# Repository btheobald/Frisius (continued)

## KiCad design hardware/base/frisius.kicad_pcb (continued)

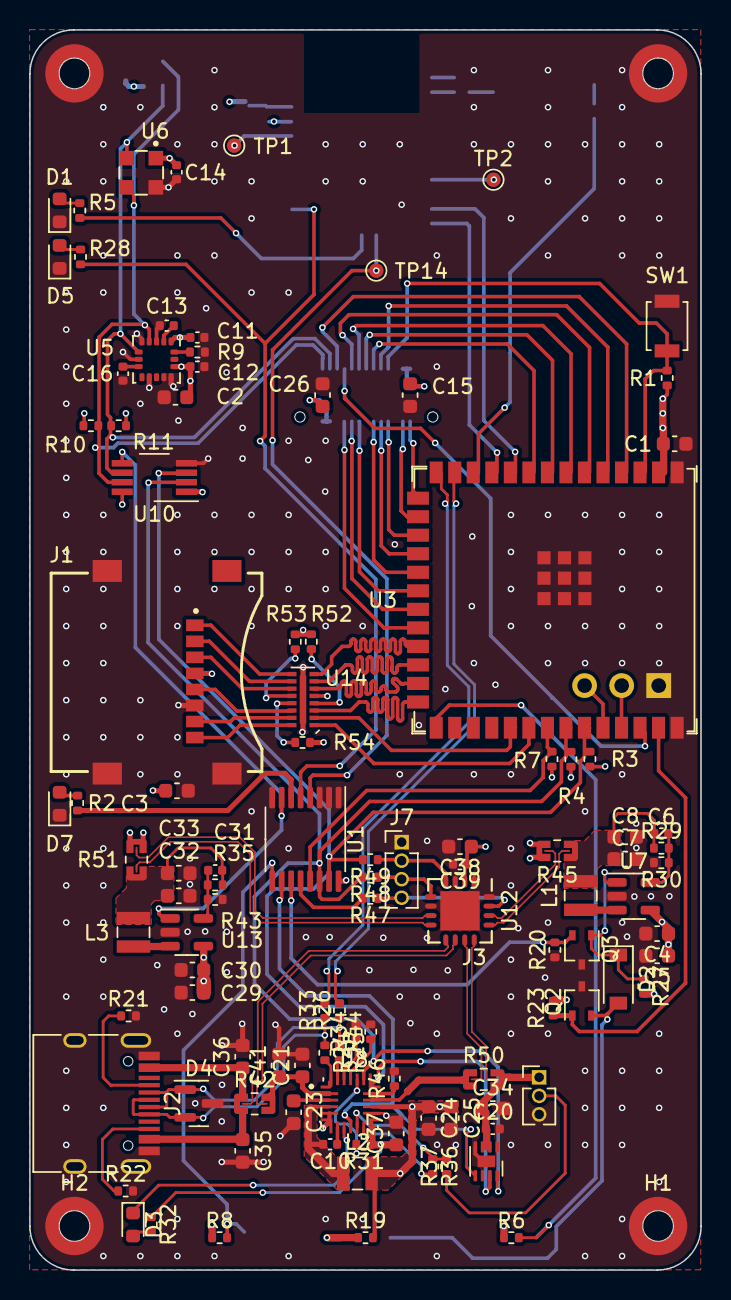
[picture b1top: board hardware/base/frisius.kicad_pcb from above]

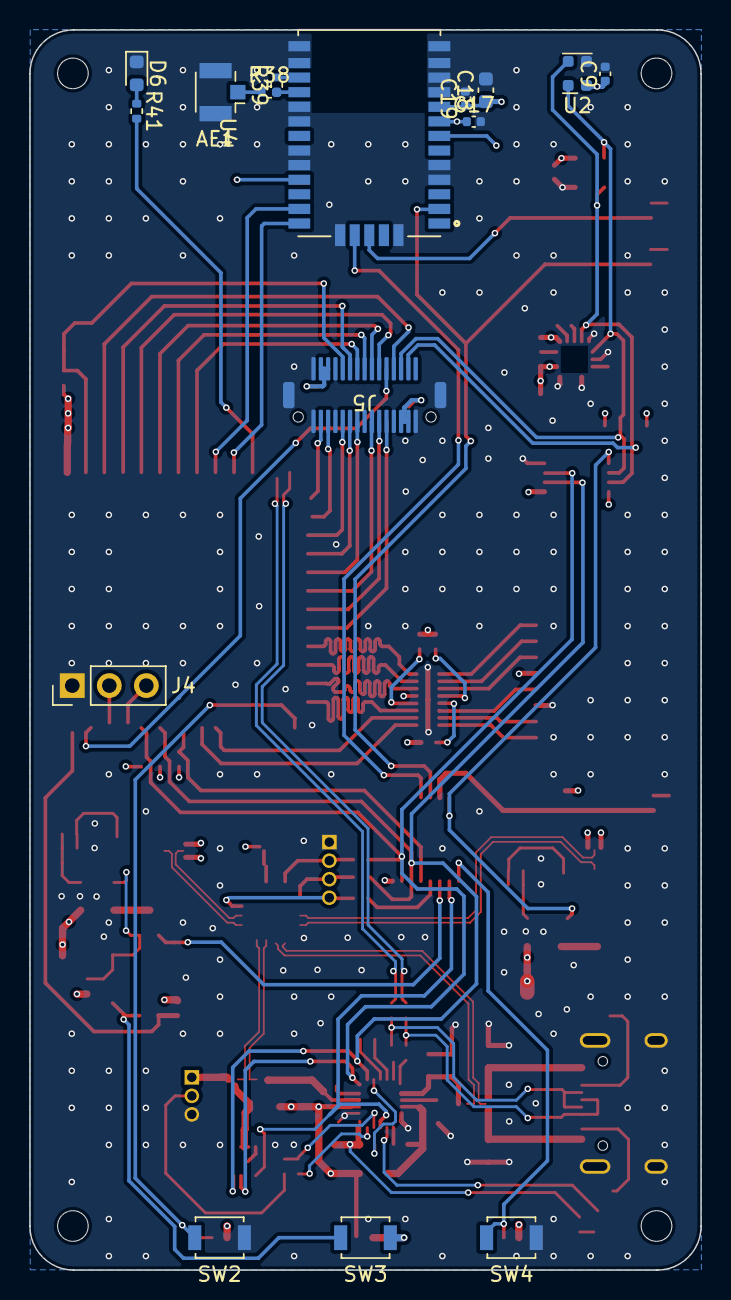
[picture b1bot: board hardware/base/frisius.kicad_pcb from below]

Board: 4 copper layers, 46.0 x 85.0 mm, 126 parts (16 on the bottom side), 113 nets.

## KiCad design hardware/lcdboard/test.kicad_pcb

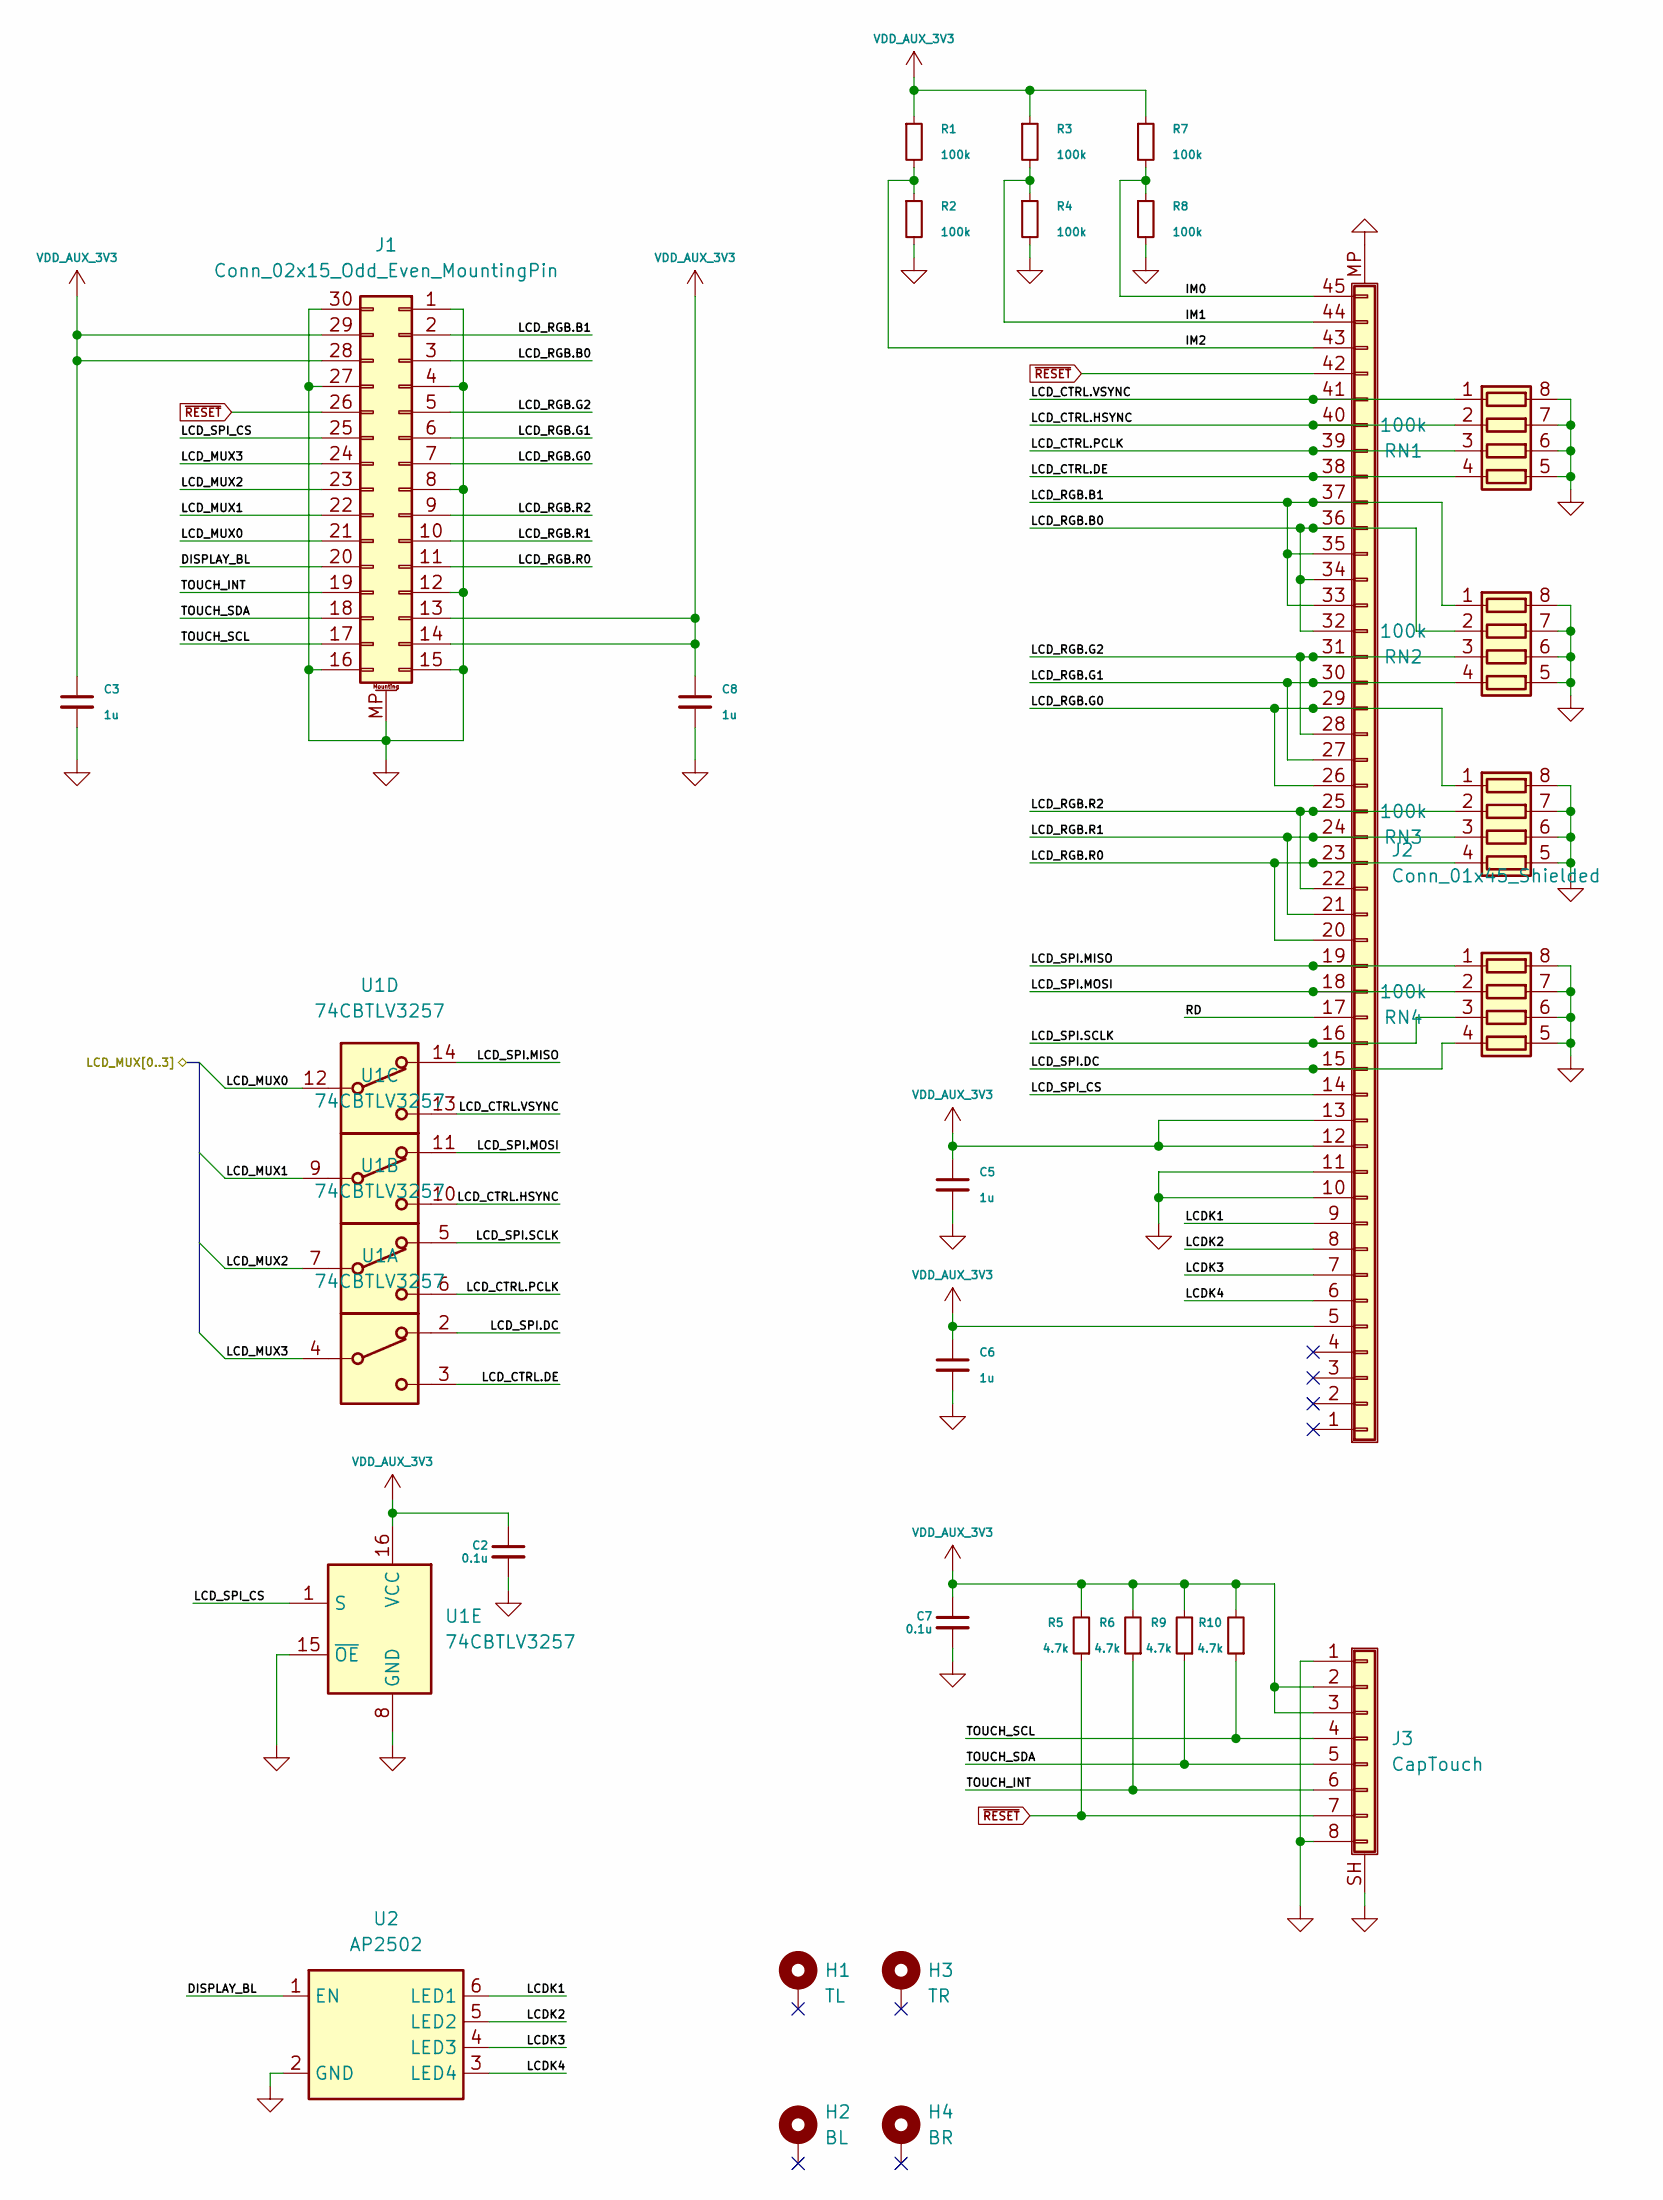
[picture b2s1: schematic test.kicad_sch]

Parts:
C2, C7: 0.1u; C_0402_1005Metric
C3, C5, C6, C8: 1u; C_0603_1608Metric
H1: TL; Mounting_Wuerth_WA-SMSI-M1.6_H2mm_9774020633
H2: BL; Mounting_Wuerth_WA-SMSI-M1.6_H2mm_9774020633
H3: TR; Mounting_Wuerth_WA-SMSI-M1.6_H2mm_9774020633
H4: BR; Mounting_Wuerth_WA-SMSI-M1.6_H2mm_9774020633
J1: Conn_02x15_Odd_Even_MountingPin; 10132798-031100LF
J2: Conn_01x45_Shielded; Hirose_FH12-45S-0.5SH_1x45-1MP_P0.50mm_Horizontal
J3: CapTouch; TE_0-1734839-8_1x08-1MP_P0.5mm_Horizontal
R1, R2, R3, R4, R7, R8: 100k; R_0402_1005Metric
R5, R6, R9, R10: 4.7k; R_0402_1005Metric
RN1, RN2, RN3, RN4: 100k; R_Array_Concave_4x0402
U1: 74CBTLV3257; TSSOP-16_4.4x5mm_P0.65mm
U2: AP2502; SOT-23-6

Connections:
/DISPLAY_BL: J1.20, U2.1 (EN)
/IM0: J2.45, R7.2, R8.1
/IM1: J2.44, R3.2, R4.1
/IM2: J2.43, R1.2, R2.1
/LCDK1: J2.9, U2.6 (LED1)
/LCDK2: J2.8, U2.5 (LED2)
/LCDK3: J2.7, U2.4 (LED3)
/LCDK4: J2.6, U2.3 (LED4)
/LCD_CTRL.DE: J2.38, RN1.4 (R4.1), U1.3
/LCD_CTRL.HSYNC: J2.40, RN1.2 (R2.1), U1.10
/LCD_CTRL.PCLK: J2.39, RN1.3 (R3.1), U1.6
/LCD_CTRL.VSYNC: J2.41, RN1.1 (R1.1), U1.13
/LCD_MUX0: J1.21, U1.12
/LCD_MUX1: J1.22, U1.9
/LCD_MUX2: J1.23, U1.7
/LCD_MUX3: J1.24, U1.4
/LCD_RGB.B0: J1.3, J2.32, J2.34, J2.36, RN2.2 (R2.1)
/LCD_RGB.B1: J1.2, J2.33, J2.35, J2.37, RN2.1 (R1.1)
/LCD_RGB.G0: J1.7, J2.26, J2.29, RN3.1 (R1.1)
/LCD_RGB.G1: J1.6, J2.27, J2.30, RN2.4 (R4.1)
/LCD_RGB.G2: J1.5, J2.28, J2.31, RN2.3 (R3.1)
/LCD_RGB.R0: J1.11, J2.20, J2.23, RN3.4 (R4.1)
/LCD_RGB.R1: J1.10, J2.21, J2.24, RN3.3 (R3.1)
/LCD_RGB.R2: J1.9, J2.22, J2.25, RN3.2 (R2.1)
/LCD_SPI.DC: J2.15, RN4.4 (R4.1), U1.2
/LCD_SPI.MISO: J2.19, RN4.1 (R1.1), U1.14
/LCD_SPI.MOSI: J2.18, RN4.2 (R2.1), U1.11
/LCD_SPI.SCLK: J2.16, RN4.3 (R3.1), U1.5
/LCD_SPI_CS: J1.25, J2.14, U1.1 (S)
/RD: J2.17
/TOUCH_INT: J1.19, J3.6, R6.1
/TOUCH_SCL: J1.17, J3.4, R10.1
/TOUCH_SDA: J1.18, J3.5, R9.1
GND: C2.2, C3.2, C5.2, C6.2, C7.2, C8.2, J1.1, J1.4, J1.8, J1.12, J1.15, J1.16, J1.27, J1.30, J1.MP (MountPin), J2.10, J2.11, J2.MP (Mount), J3.1, J3.8, J3.SH (Shield), R2.2, R4.2, R8.2, RN1.5 (R4.2), RN1.6 (R3.2), RN1.7 (R2.2), RN1.8 (R1.2), RN2.5 (R4.2), RN2.6 (R3.2), RN2.7 (R2.2), RN2.8 (R1.2), RN3.5 (R4.2), RN3.6 (R3.2), RN3.7 (R2.2), RN3.8 (R1.2), RN4.5 (R4.2), RN4.6 (R3.2), RN4.7 (R2.2), RN4.8 (R1.2), U1.8 (GND), U1.15 (~OE), U2.2 (GND)
VDD_AUX_3V3: C2.1, C3.1, C5.1, C6.1, C7.1, C8.1, J1.13, J1.14, J1.28, J1.29, J2.5, J2.12, J2.13, J3.2, J3.3, R1.1, R3.1, R5.2, R6.2, R7.1, R9.2, R10.2, U1.16 (VCC)
~RESET: J1.26, J2.42, J3.7, R5.1

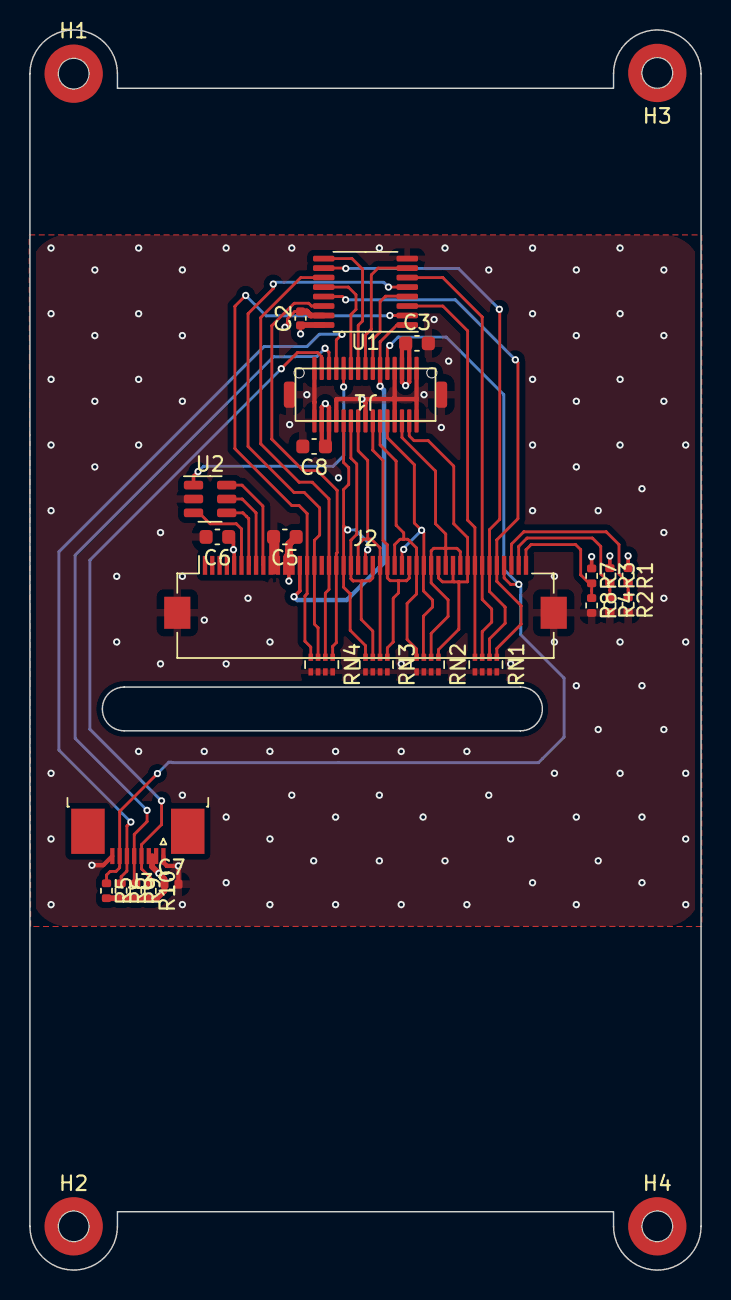
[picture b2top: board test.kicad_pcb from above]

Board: 4 copper layers, 46.0 x 85.0 mm, 29 parts (0 on the bottom side), 35 nets.

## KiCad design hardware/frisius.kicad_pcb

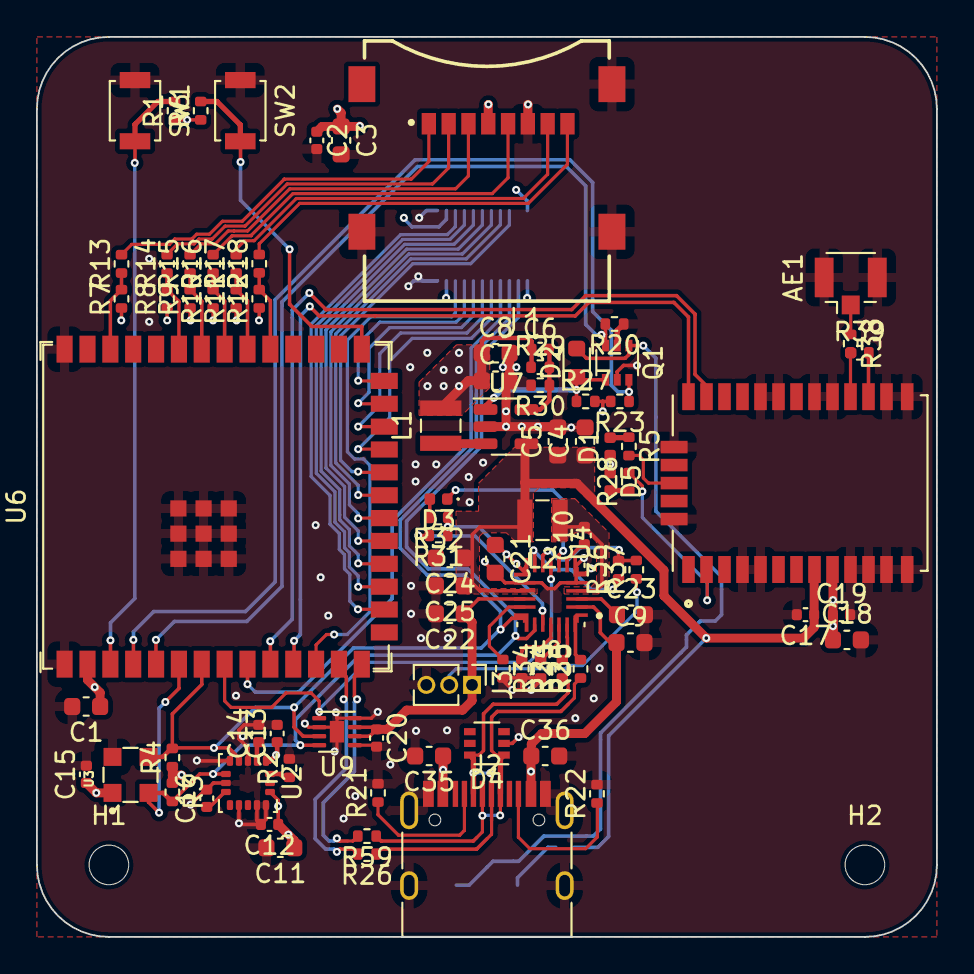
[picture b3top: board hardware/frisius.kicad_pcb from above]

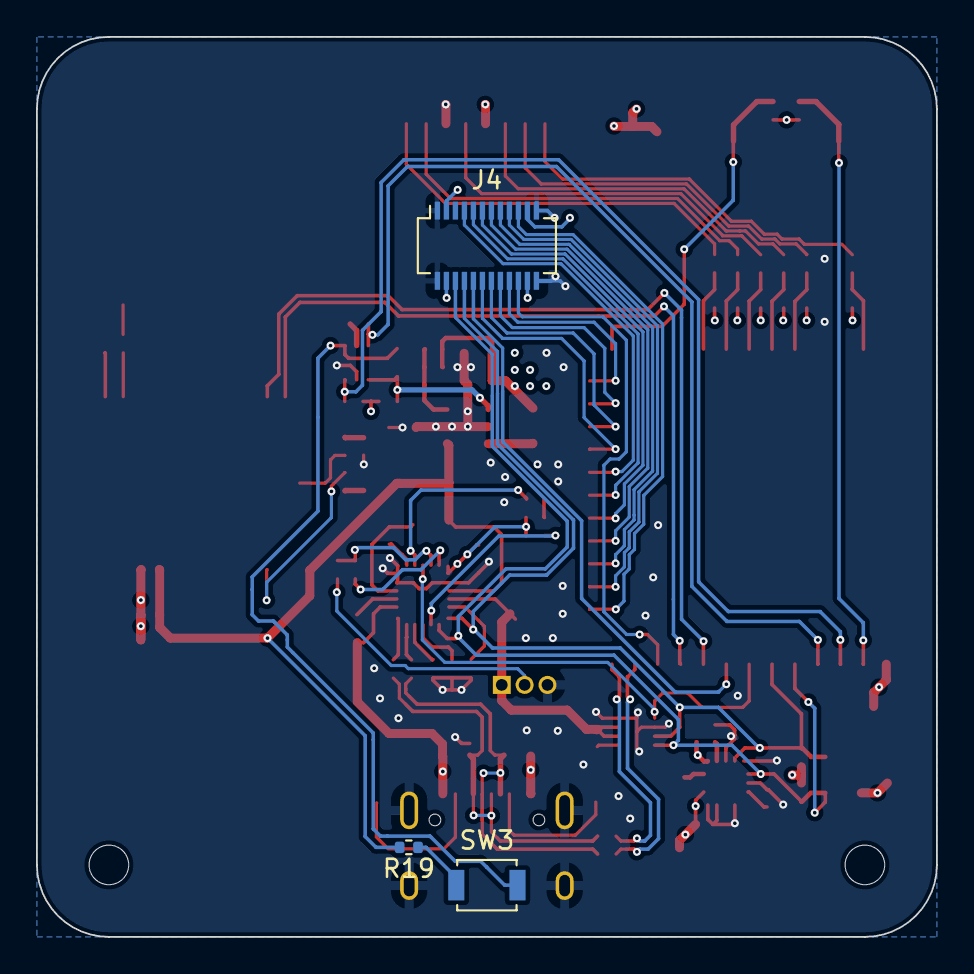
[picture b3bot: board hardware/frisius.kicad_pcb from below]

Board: 4 copper layers, 50.0 x 50.0 mm, 93 parts (4 on the bottom side), 75 nets.

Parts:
AE1: Antenna_Shield; U.FL_Hirose_U.FL-R-SMT-1_Vertical
C1, C3, C4, C5, C9, C11, C18, C35, C36: 4.7u; C_0603_1608Metric
C2, C10, C12, C13, C14, C15, C16, C17, C19, C20: 0.1u; C_0402_1005Metric
C6: 10p; C_0402_1005Metric
C7, C8, C21, C22, C23, C24, C25: 10u; C_0603_1608Metric
D1, D3, D5: LED_Small_Filled; LED_0402_1005Metric
D2: MBR0540; LED_0603_1608Metric
D4: ESD5V5U5ULCE6327HTSA1; SOT-363_SC-70-6
H1: BL; MountingHole_2.2mm_M2_ISO7380
H2: BR; MountingHole_2.2mm_M2_ISO7380
J1: MEM2067; GCT_MEM2067-02-180-00-A_REVB
J2: USB_C_Receptacle_USB2.0; USB_C_Receptacle_HRO_TYPE-C-31-M-12
J3: BATTERY; PinHeader_1x03_P1.27mm_Vertical
J4: Display; Molex_SlimStack_55560-0241_2x12_P0.50mm_Vertical
L1: 1u; L_Wuerth_MAPI-2510
L2: 0.47u; L_Wuerth_MAPI-2510
N6: Display Board; WEEE-Logo_4.2x6mm_SilkScreen
Q1: Q_Dual_NMOS_G1S2G2D2S1D1; SOT-363_SC-70-6
R1, R6: R_Small; R_0402_1005Metric
R2, R7, R8, R9, R10, R11, R12: 10k; R_0402_1005Metric
R3, R4: 4.7k; R_0402_1005Metric
R5, R28, R31, R32: 1k; R_0402_1005Metric
R13, R14, R15, R16, R17, R18: 22; R_0402_1005Metric
R19, R20, R23, R27, R30: 100k; R_0402_1005Metric
R21, R22, R24, R25, R26, R33, R34, R38, R39, R59: 0; R_0402_1005Metric
R29: ?; R_0402_1005Metric
R35, R36, R37: 14k; R_0402_1005Metric
SW1: RESET; SW_SPST_B3U-1000P
SW2: BOOT; SW_SPST_B3U-1000P
SW3: POWER; SW_SPST_B3U-1000P
U2: FXOS8700CQR1; LGA-16_3x3mm_P0.5mm_LayoutBorder3x5y
U3: MS5637-02BA03; TE_MS563702BA03-50
U4: L96-M33; Quectel_L96-M33
U6: ESP32-S3-WROOM-1; ESP32-S3-WROOM-1U
U7: TLV62569DBV; SOT-23-5
U8: MP2723; MP_QFN-26-3.5x3.5_P0.45mm
U9: MAX17048G; TDFN-8-1EP_2x2mm_P0.5mm_EP0.8x1.2mm

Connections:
+3V3: C1.1, C2.1, C3.1, C6.1, C7.1, C8.1, C11.1, C12.1, C13.1, C15.1, C18.1, C19.1, J1.4 (VDD), J4.3, J4.4, J4.21, J4.22, L1.2, R1.1, R3.1, R4.1, R6.1, R7.1, R8.1, R9.1, R10.1, R11.1, R12.1, R23.2, R27.2, R29.1, U2.1 (VDDIO), U2.14 (VDD), U3.1 (VDD), U4.9 (VCC), U6.2 (3V3)
+BATT: C20.1, C22.1, J3.1, U8.17 (BATT), U9.2 (CELL), U9.3 (VDD)
/Display/DISPLAY_BL: J4.19, U6.16 (GPIO46)
/Display/LCD_SPI_CTRL: J4.20, U6.12 (GPIO8/TOUCH8/ADC1_CH7/SUBSPICS1)
/Display/MUXLINE0: J4.12, U6.23 (GPIO21)
/Display/MUXLINE1: J4.14, U6.24 (GPIO47/SPICLK_P/SUBSPICLK_P_DIFF)
/Display/MUXLINE2: J4.16, U6.25 (GPIO48/SPICLK_N/SUBSPICLK_N_DIFF)
/Display/MUXLINE3: J4.18, U6.26 (GPIO45)
/Display/RGB.B0: J4.9, U6.21 (GPIO13/TOUCH13/ADC2_CH2/FSPIQ/FSPIIO7/S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)
/Display/RGB.B1: J4.7, U6.22 (GPIO14/TOUCH14/ADC2_CH3/FSPIWP/FSPIDQS/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)
/Display/RGB.G0: J4.13, U6.19 (GPIO11/TOUCH11/ADC2_CH0/FSPID/FSPIIO5/S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)
/Display/RGB.G1: J4.11, U6.20 (GPIO12/TOUCH12/ADC2_CH1/FSPICLK/FSPIIO6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)
/Display/RGB.R0: J4.17, U6.17 (GPIO9/TOUCH9/ADC1_CH8/FSPIHD/SUBSPIHD)
/Display/RGB.R1: J4.15, U6.18 (GPIO10/TOUCH10/ADC1_CH9/FSPICS0/FSPIIO4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)
/Display/SYS_I2C.SCL: J4.8, R4.2, U2.4 (SCL/SCLK), U3.3 (SCL), U6.7 (GPIO7/TOUCH7/ADC1_CH6), U8.19-20 (SCL), U9.7 (SCL)
/Display/SYS_I2C.SDA: J4.6, R3.2, U2.6 (SDA/MOSI), U3.2 (SDA), U6.6 (GPIO6/TOUCH6/ADC1_CH5), U8.21 (SDA), U9.8 (SDA)
/Display/TOUCH_INT: J4.10, U6.9 (GPIO16/U0CTS/ADC2_CH5/XTAL_32K_NH5)
/GPS/ANT_RF: AE1.1 (A), R38.1
/GPS/GPS_RF: R38.2, R39.1, U4.17 (RF_IN)
/GPS/GPS_UART.RX: U4.25 (TXD1), U6.10 (GPIO17/U1TXD/ADC2_CH6)
/GPS/GPS_UART.TX: U4.26 (RXD1), U6.11 (GPIO18/U1RXD/ADC2_CH7/CLK_OUT3)
/GPS/L96_1PPS: R5.2, U4.29 (1PPS)
/GPS/L96_FIX: R28.2, U4.2 (3D_FIX)
/GPS/MOD_RF: R39.2, U4.16 (RF_OUT)
/Power/BMS_INT: U6.8 (GPIO15/U0RTS/ADC2_CH4/XTAL_32K_P), U8.10 (INT), U9.5 (~ALRT)
/Power/PORT_D+: D4.1 (K), J2.A6 (D+), J2.B6 (D+), R25.1, R59.1
/Power/PORT_D-: D4.6 (K), J2.A7 (D-), J2.B7 (D-), R24.1, R26.1
/Power/POWER_BUTTON: Q1.6 (D), R23.1, U6.4 (GPIO4/TOUCH4/ADC1_CH3)
/Power/SHUTDOWN: Q1.3 (G), R20.2, U6.5 (GPIO5/TOUCH5/ADC1_CH4)
/Power/USB_CHG.D+: R25.2, U8.1-26 (DP)
/Power/USB_CHG.D-: R24.2, U8.25 (DM)
/Power/USB_ESP.D+: R59.2, U6.14 (GPIO20/U1CTS/ADC2_CH9/CLK_OUT1/USB_D+)
/Power/USB_ESP.D-: R26.2, U6.13 (GPIO19/U1RTS/ADC2_CH8/CLK_OUT2/USB_D-)
/Power/VREF: C21.1, R31.1, R32.1, U8.13-14 (VREF)
/Processor/BOOT_BTN: R6.2, SW2.2, U6.27 (GPIO0/BOOT)
/Processor/RST_BTN: R1.2, SW1.2, U6.3 (EN)
/Processor/SDMMC.CLK: R10.2, R16.1, U6.33 (MTDO/GPIO40/CLK_OUT2)
/Processor/SDMMC.CMD: R9.2, R15.1, U6.34 (MTDI/GPIO41/CLK_OUT1)
/Processor/SDMMC.D0: R11.2, R17.1, U6.32 (MTCK/GPIO39/CLK_OUT3/SUBSPICS1)
/Processor/SDMMC.D1: R12.2, R18.1, U6.31 (GPIO38/FSPIWP/SUBSPIWP)
/Processor/SDMMC.D2: R7.2, R13.1, U6.38 (GPIO2/TOUCH2/ADC1_CH1)
/Processor/SDMMC.D3: R8.2, R14.1, U6.35 (MTMS/GPIO42)
GND: AE1.2 (Shield), C1.2, C2.2, C3.2, C4.2, C5.2, C7.2, C8.2, C9.2, C11.2, C12.2, C13.2, C14.2, C15.2, C16.2, C17.2, C18.2, C19.2, C20.2, C21.2, C22.2, C23.2, C24.2, C25.2, C35.2, C36.2, D1.1 (K), D4.2 (A), D5.1 (K), J1.6 (VSS), J1.9 (DET_B), J1.10 (DET_A), J1.11 (SHIELD), J2.A1 (GND), J2.A12 (GND), J2.B1 (GND), J2.B12 (GND), J2.S1 (SHIELD), J3.3, J4.1, J4.2, J4.23, J4.24, Q1.2 (S), Q1.5 (S), R2.2, R20.1, R21.2, R22.2, R30.2, R33.2, R34.2, R35.2, SW1.1, SW2.1, U2.3 (RSVD), U2.5 (GND), U2.7 (SA0/MISO), U2.10 (SA1/CS_B), U2.12 (GND), U2.13 (RSVD), U3.4 (GND), U4.4 (GND), U4.5 (GND), U4.10 (GND), U4.11 (GND), U4.12 (GND), U4.13 (GND), U4.14 (GND), U4.15 (GND), U4.18 (GND), U4.19 (GND), U4.21 (GND), U4.22 (GND), U4.27 (GND), U4.31 (GND), U6.1 (GND), U6.40 (GND), U6.41 (GND), U7.2 (GND), U8.5 (PGND), U8.6-7 (PGND), U8.15 (AGND), U9.1 (CTG), U9.4 (GND), U9.6 (QSTRT), U9.9 (PAD)
unnamed: C6.2, R29.2, R30.1, U7.5 (FB)
unnamed: C10.1, U8.8 (BST)
unnamed: C10.2, L2.1, U8.4 (SW)
unnamed: C14.1, U2.2 (BYP)
unnamed: C16.1, U2.8 (CRST)
unnamed: C23.1, U8.3 (PMID)
unnamed: D1.2 (A), R5.1
unnamed: D2.1 (K), Q1.4 (D), R27.1, U7.1 (EN)
unnamed: D2.2 (A), Q1.1 (G), SW3.2
unnamed: D3.1 (K), U8.9 (STAT)
unnamed: D3.2 (A), R32.2
unnamed: D5.2 (A), R28.1
unnamed: J1.1 (DAT2), R13.2
unnamed: J1.2 (DAT3/CD), R14.2
unnamed: J1.3 (CMD), R15.2
unnamed: J1.5 (CLK), R16.2
unnamed: J1.7 (DAT0), R17.2
unnamed: J1.8 (DAT1), R18.2
unnamed: J2.A5 (CC1), R21.1
unnamed: J2.B5 (CC2), R22.1
unnamed: J3.2, R37.1
unnamed: L1.1, U7.3 (SW)
unnamed: R2.1, U2.16 (RST)
unnamed: R19.1, SW3.1
unnamed: R31.2, U8.22 (DISC)
unnamed: R33.1, U8.23 (OTG)
unnamed: R34.1, U8.18 (~CE)
unnamed: R35.1, U8.24 (ILIM)
unnamed: R36.1, U8.12 (VNTC)
unnamed: R36.2, R37.2, U8.11 (NTC)
VBUS: C9.1, C35.1, C36.1, J2.A4 (VBUS), J2.A9 (VBUS), J2.B4 (VBUS), J2.B9 (VBUS), U8.2 (IN)
VDD_NVDC: C4.1, C5.1, C17.1, C24.1, C25.1, L2.2, R19.2, U4.8 (V_BCKP), U7.4 (VIN), U8.16 (SYS)

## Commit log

2021-12-18 Pushing hardware work done so far
2021-12-18 Added bt_ki_libs as submodule
2021-12-19 train schematics
2021-12-21 usb, charger, sensors, heir
2021-12-21 usb, bms, proc, btn changes
2021-12-21 started b2b and power
2021-12-22 ready for first review
2021-12-23 checking footprint assignment, added current sense pac1934 for dev
2021-12-28 hardware update
2021-12-29 initial component placement and design simplification
2021-12-30 fixing submodule
2021-12-30 properly fixing submodules
2021-12-30 really actually fixed submodule
2021-12-30 removed submodule
2021-12-30 flushing out
2021-12-30 refreshed ki_libs to track main
2021-12-31 schematic tidy up, component placement, shielding investigation
2022-01-02 minor sch tweaks, more layout, added power emc shield
2022-01-05 screen mock, tweaked layout easier powerplane division
2022-06-19 Added ESP32-S3-WROOM
2022-06-20 changing sdmmc to spi to support lcd rgb mode
2022-06-26 layout 0 unconnected
2022-06-28 fixed dsheet link names
2022-08-03 merged in lcdboard test work
2022-08-08 restructure, adding branch for mux'd display board
2022-08-09 added 74CBLTV3257
2022-09-20 schematic complete unreviewed
2022-09-21 placed components on board - rough
2022-09-22 further placement, pre condense
2022-09-22 Testing condensed layout
2022-09-24 split back out condensed board into lcdboard and base
2022-09-25 completed layout for lcdboard prototype, may need to move b2b down for clearance on mainboard.
2022-09-27 relayout screen
2022-09-28 testing viastiching
2022-10-01 screen design freeze, 3d model added to base, routed display connector, sd, usb
2022-10-02 layout
2022-10-03 more layout, optimising i2c
2022-10-03 layout complete, drc checks and tweaks to silkscreen, attempting geo reannotate
2022-10-03 Tidied up, added more stitches
